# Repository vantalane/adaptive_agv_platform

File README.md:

# adaptive_agv_platform
Fontys adaptive robotics AGV platform design repository.

## Design files roadmap

Specifications and board information can be found in the "documentation" folder.

Design sources are aptly placed within design_sources folder. These include kicad files, production files and example code.

## PCBA production

Necessary files and information regarding ordering, assembly and part sourcing are packaged together with PCB versions.

These files can be found within 
``` design_sources/KiCAD/controller_mainboard_vX/production``` \
with ```vX``` being version number.

Instruction for production are found within the ```production``` folder. 
Currently, only V0.1 is available.

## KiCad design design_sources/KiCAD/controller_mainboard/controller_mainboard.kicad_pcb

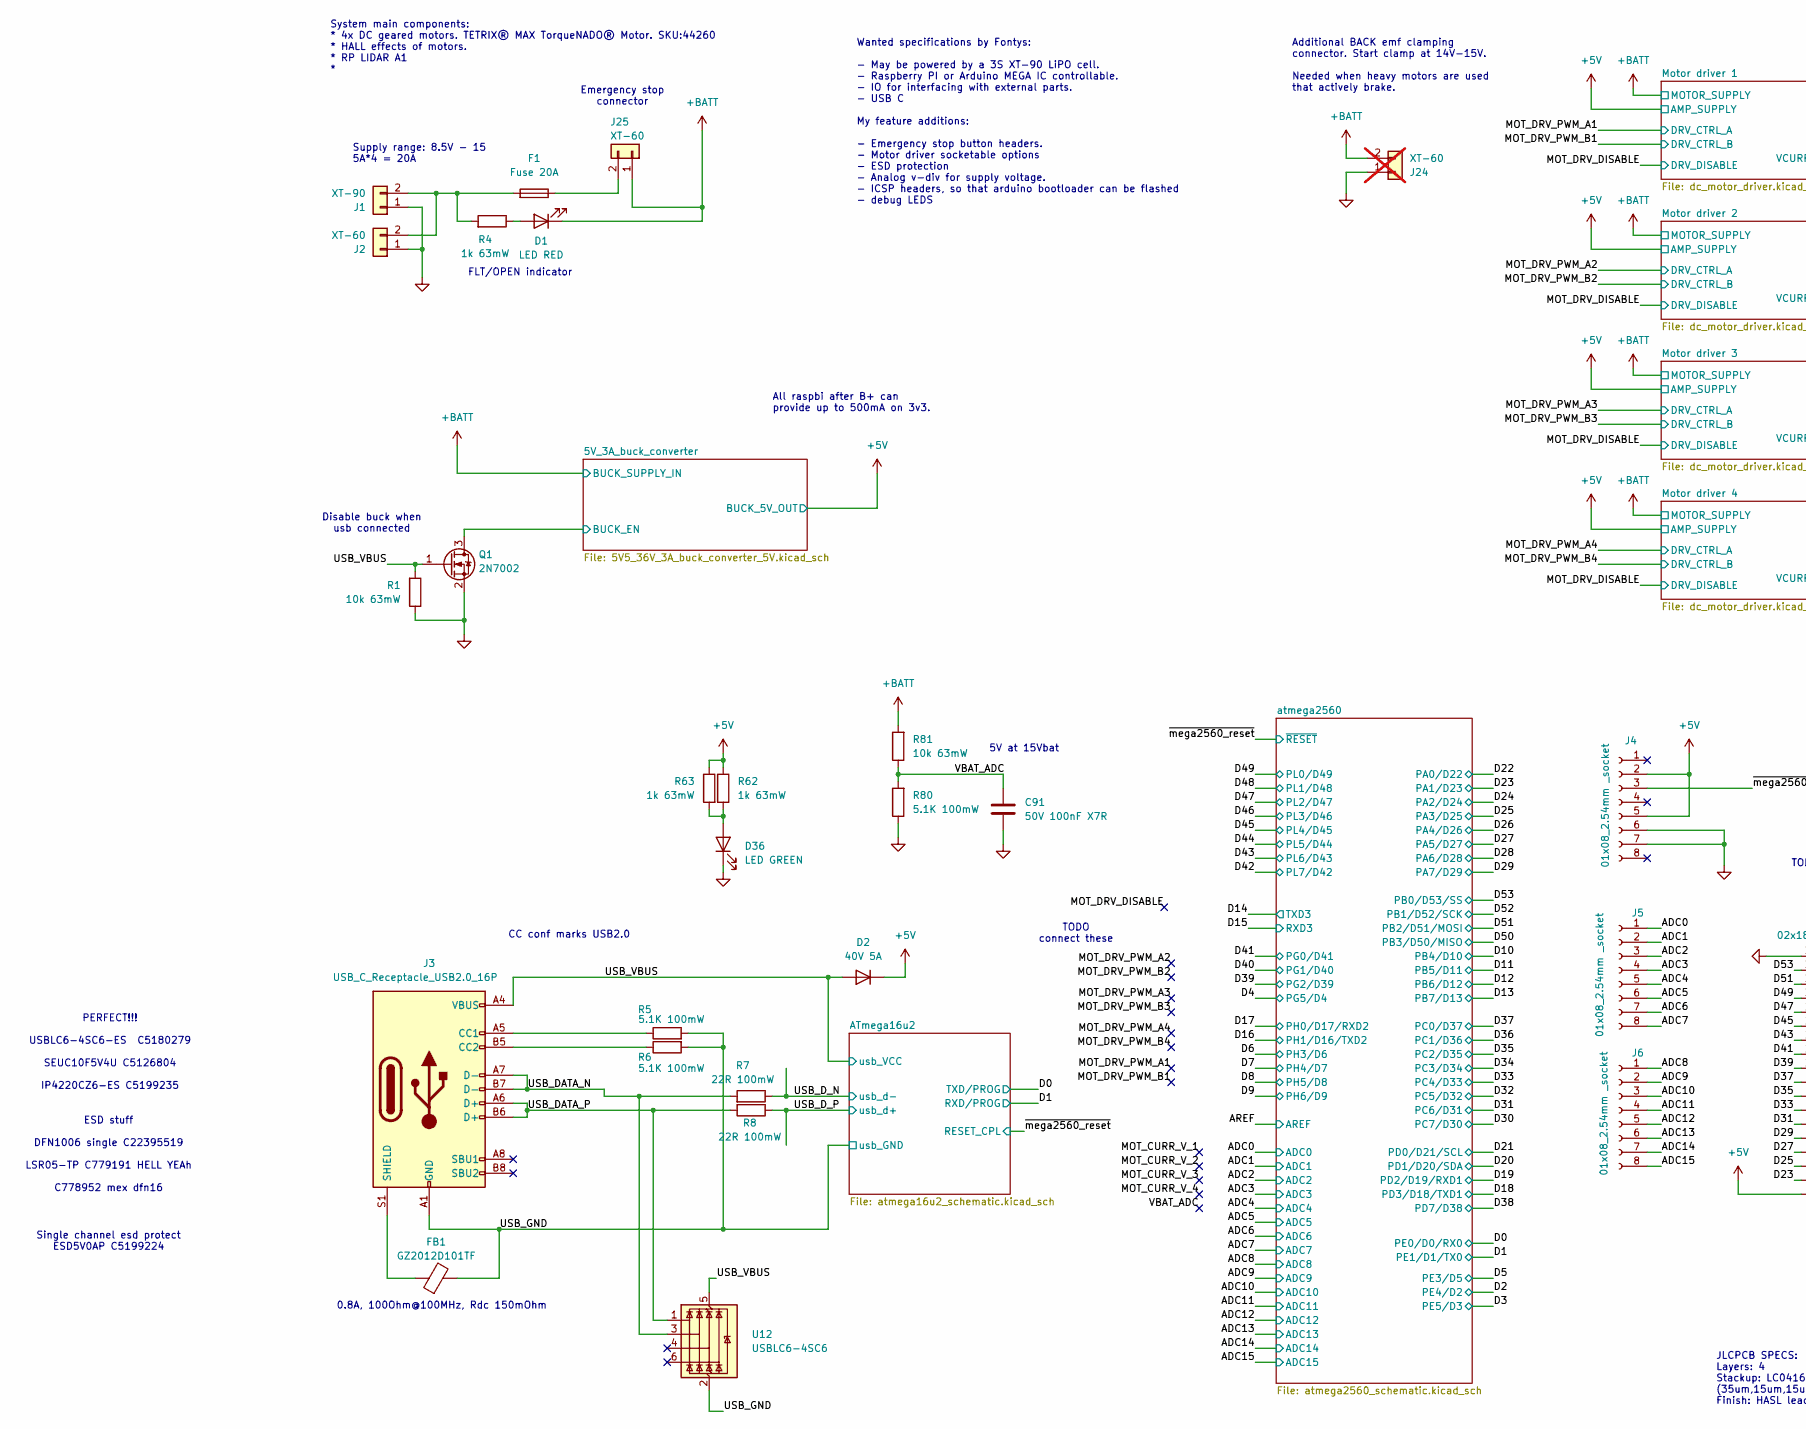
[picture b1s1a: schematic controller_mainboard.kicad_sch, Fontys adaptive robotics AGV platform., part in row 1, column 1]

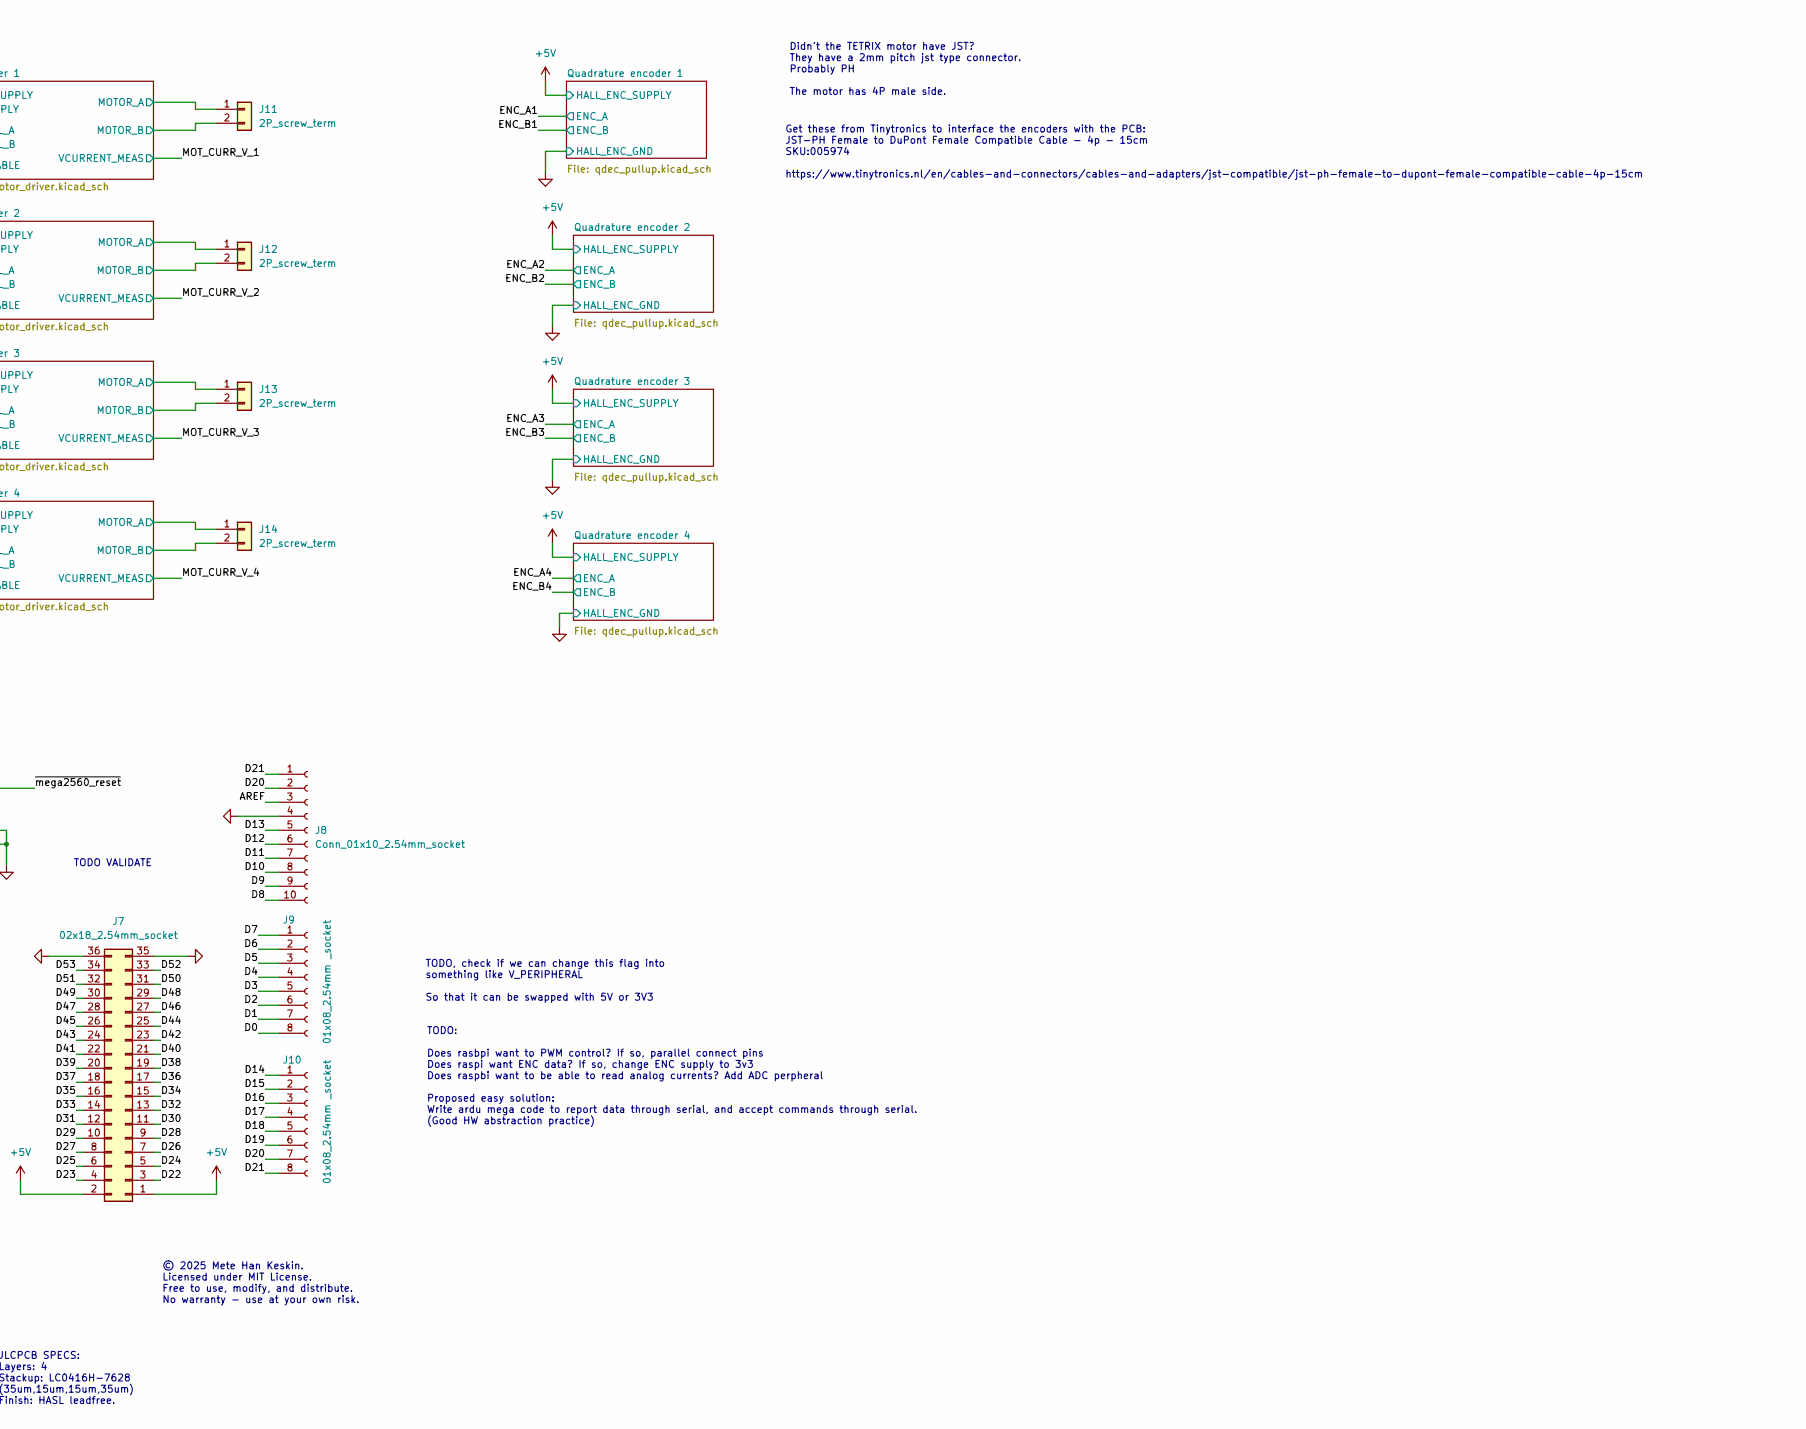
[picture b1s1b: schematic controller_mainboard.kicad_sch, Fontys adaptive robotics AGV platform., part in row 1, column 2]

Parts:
C91: 50V 100nF X7R; C_0603_1608Metric; JLCPCB C14663
D1: LED RED; LED_0603_1608Metric; JLCPCB C2286
D2: 40V 5A; D_SMA; JLCPCB C22452
D36: LED GREEN; LED_0805_2012Metric; JLCPCB C2297
F1: Fuse 20A; BLX-A fuse holder
FB1: GZ2012D101TF; L_0805_2012Metric; JLCPCB C1015
J1: XT-90; XT-90_Connector
J2, J25: XT-60; AMASS_XT60-M_1x02_P7.20mm_Vertical
J3: USB_C_Receptacle_USB2.0_16P; USB_C_Receptacle_GCT_USB4105-xx-A_16P_TopMnt_Horizontal; JLCPCB C2927038
J4, J5, J6, J9, J10: 01x08_2.54mm _socket; PinSocket_1x08_P2.54mm_Vertical
J7: 02x18_2.54mm_socket; PinHeader_2x18_P2.54mm_Vertical
J8: Conn_01x10_2.54mm_socket; PinSocket_1x10_P2.54mm_Vertical
J11, J12, J13, J14: 2P_screw_term; JST_NV_B02P-NV_1x02_P5.00mm_Vertical
J24: XT-60; AMASS_XT60-M_1x02_P7.20mm_Vertical; not fitted
Q1: 2N7002; SOT-23; JLCPCB C8545
R1, R81: 10k 63mW; R_0402_1005Metric; JLCPCB C25744
R4, R62, R63: 1k 63mW; R_0402_1005Metric; JLCPCB C11702
R5, R6, R80: 5.1K 100mW; C_0603_1608Metric; JLCPCB C23186
R7, R8: 22R 100mW; R_0603_1608Metric; JLCPCB C23345
U12: USBLC6-4SC6; SOT-23-6; JLCPCB C5180279

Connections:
+5V: D2.1 (K), J4.2, J4.5, J7.1, J7.2, R62.1, R63.1; also elsewhere on the board
+BATT: D1.1 (K), J24.2, J25.1, R81.2; also elsewhere on the board
/5V_3A_buck_converter/BUCK_EN: Q1.3 (D); also elsewhere on the board
/ADC0: J5.1; also elsewhere on the board
/ADC1: J5.2; also elsewhere on the board
/ADC2: J5.3; also elsewhere on the board
/ADC3: J5.4; also elsewhere on the board
/ADC4: J5.5; also elsewhere on the board
/ADC5: J5.6; also elsewhere on the board
/ADC6: J5.7; also elsewhere on the board
/ADC7: J5.8; also elsewhere on the board
/ADC8: J6.1; also elsewhere on the board
/ADC9: J6.2; also elsewhere on the board
/ADC10: J6.3; also elsewhere on the board
/ADC11: J6.4; also elsewhere on the board
/ADC12: J6.5; also elsewhere on the board
/ADC13: J6.6; also elsewhere on the board
/ADC14: J6.7; also elsewhere on the board
/ADC15: J6.8; also elsewhere on the board
/AREF: J8.3; also elsewhere on the board
/D0: J9.8; also elsewhere on the board
/D1: J9.7; also elsewhere on the board
/D2: J9.6; also elsewhere on the board
/D3: J9.5; also elsewhere on the board
/D4: J9.4; also elsewhere on the board
/D5: J9.3; also elsewhere on the board
/D6: J9.2; also elsewhere on the board
/D7: J9.1; also elsewhere on the board
/D8: J8.10; also elsewhere on the board
/D9: J8.9; also elsewhere on the board
/D10: J8.8; also elsewhere on the board
/D11: J8.7; also elsewhere on the board
/D12: J8.6; also elsewhere on the board
/D13: J8.5; also elsewhere on the board
/D14: J10.1; also elsewhere on the board
/D15: J10.2; also elsewhere on the board
/D16: J10.3; also elsewhere on the board
/D17: J10.4; also elsewhere on the board
/D18: J10.5; also elsewhere on the board
/D19: J10.6; also elsewhere on the board
/D20: J8.2, J10.7; also elsewhere on the board
/D21: J8.1, J10.8; also elsewhere on the board
/D22: J7.3; also elsewhere on the board
/D23: J7.4; also elsewhere on the board
/D24: J7.5; also elsewhere on the board
/D25: J7.6; also elsewhere on the board
/D26: J7.7; also elsewhere on the board
/D27: J7.8; also elsewhere on the board
/D28: J7.9; also elsewhere on the board
/D29: J7.10; also elsewhere on the board
/D30: J7.11; also elsewhere on the board
/D31: J7.12; also elsewhere on the board
/D32: J7.13; also elsewhere on the board
/D33: J7.14; also elsewhere on the board
/D34: J7.15; also elsewhere on the board
/D35: J7.16; also elsewhere on the board
/D36: J7.17; also elsewhere on the board
/D37: J7.18; also elsewhere on the board
/D38: J7.19; also elsewhere on the board
/D39: J7.20; also elsewhere on the board
/D40: J7.21; also elsewhere on the board
/D41: J7.22; also elsewhere on the board
/D42: J7.23; also elsewhere on the board
/D43: J7.24; also elsewhere on the board
/D44: J7.25; also elsewhere on the board
/D45: J7.26; also elsewhere on the board
/D46: J7.27; also elsewhere on the board
/D47: J7.28; also elsewhere on the board
/D48: J7.29; also elsewhere on the board
/D49: J7.30; also elsewhere on the board
/D50: J7.31; also elsewhere on the board
/D51: J7.32; also elsewhere on the board
/D52: J7.33; also elsewhere on the board
/D53: J7.34; also elsewhere on the board
/Motor driver 1/MOT_SIDE_A: J11.1; also elsewhere on the board
/Motor driver 1/MOT_SIDE_B: J11.2; also elsewhere on the board
/Motor driver 2/MOT_SIDE_A: J12.1; also elsewhere on the board
/Motor driver 2/MOT_SIDE_B: J12.2; also elsewhere on the board
/Motor driver 3/MOT_SIDE_A: J13.1; also elsewhere on the board
/Motor driver 3/MOT_SIDE_B: J13.2; also elsewhere on the board
/Motor driver 4/MOT_SIDE_A: J14.1; also elsewhere on the board
/Motor driver 4/MOT_SIDE_B: J14.2; also elsewhere on the board
/USB_DATA_N: J3.A7 (D-), J3.B7 (D-), R7.2, U12.3 (I/O2)
/USB_DATA_P: J3.A6 (D+), J3.B6 (D+), R8.2, U12.1 (I/O1)
/USB_D_N: R7.1; also elsewhere on the board
/USB_D_P: R8.1; also elsewhere on the board
/USB_GND: FB1.2, J3.A1 (GND), J3.A12 (GND), J3.B1 (GND), J3.B12 (GND), R5.2, R6.2, U12.2 (GND); also elsewhere on the board
/USB_VBUS: D2.2 (A), J3.A4 (VBUS), J3.A9 (VBUS), J3.B4 (VBUS), J3.B9 (VBUS), Q1.1 (G), R1.2, U12.5 (VBUS); also elsewhere on the board
/VBAT_ADC: C91.2, R80.2, R81.1
/~mega2560_reset: J4.3; also elsewhere on the board
GND: C91.1, D36.1 (K), J1.1, J2.1, J4.6, J4.7, J7.35, J7.36, J8.4, J24.1, Q1.2 (S), R1.1, R80.1; also elsewhere on the board
unnamed: D1.2 (A), R4.1
unnamed: D36.2 (A), R62.2, R63.2
unnamed: F1.2, J1.2, J2.2, R4.2
unnamed: J3.A5 (CC1), R5.1
unnamed: J3.B5 (CC2), R6.1
unnamed: FB1.1, J3.S1 (SHIELD)
unnamed: F1.1, J25.2

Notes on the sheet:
Get these from Tinytronics to interface the encoders with the PCB: JST-PH Female to DuPont Female Compatible Cable - 4p - 15cm SKU:005974 https://www.tinytronics.nl/en/cables-and-connectors/cables-and-adapters/jst-compatible/jst-ph-female-to-dupont-female-compatible-cable-4p-15cm
JLCPCB SPECS: Layers: 4 Stackup: LC0416H-7628 (35um,15um,15um,35um) Finish: HASL leadfree.
Emergency stop connector
Wanted specifications by Fontys: - May be powered by a 3S XT-90 LiPO cell. - Raspberry PI or Arduino MEGA IC controllable. - IO for interfacing with external parts. - USB C My feature additions: - Emergency stop button headers. - Motor driver socketable options - ESD protection - Analog v-div for s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
© 2025 Mete Han Keskin. Licensed under MIT License. Free to use, modify, and distribute. No warranty - use at your own risk.
5A*4 = 20A
ESD stuff DFN1006 single C22395519 LSR05-TP C779191 HELL YEAh C778952 mex dfn16
0.8A, 100Ohm@100MHz, Rdc 150mOhm
TODO VALIDATE
Supply range: 8.5V - 15
All raspbi after B+ can provide up to 500mA on 3v3.
FLT/OPEN indicator
CC conf marks USB2.0
System main components: * 4x DC geared motors. TETRIX® MAX TorqueNADO® Motor. SKU:44260 * HALL effects of motors. * RP LIDAR A1 *
Disable buck when usb connected
TODO: Does rasbpi want to PWM control? If so, parallel connect pins Does raspi want ENC data? If so, change ENC supply to 3v3 Does raspbi want to be able to read analog currents? Add ADC perpheral Proposed easy solution: Write ardu mega code to report data through serial, and accept commands throug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
Didn't the TETRIX motor have JST? They have a 2mm pitch jst type connector. Probably PH The motor has 4P male side.
TODO connect these
PERFECT!!! USBLC6-4SC6-ES C5180279 SEUC10F5V4U C5126804 IP4220CZ6-ES C5199235
5V at 15Vbat
TODO, check if we can change this flag into something like V_PERIPHERAL So that it can be swapped with 5V or 3V3
Single channel esd protect ESD5V0AP C5199224
Additional BACK emf clamping connector. Start clamp at 14V-15V. Needed when heavy motors are used that actively brake.

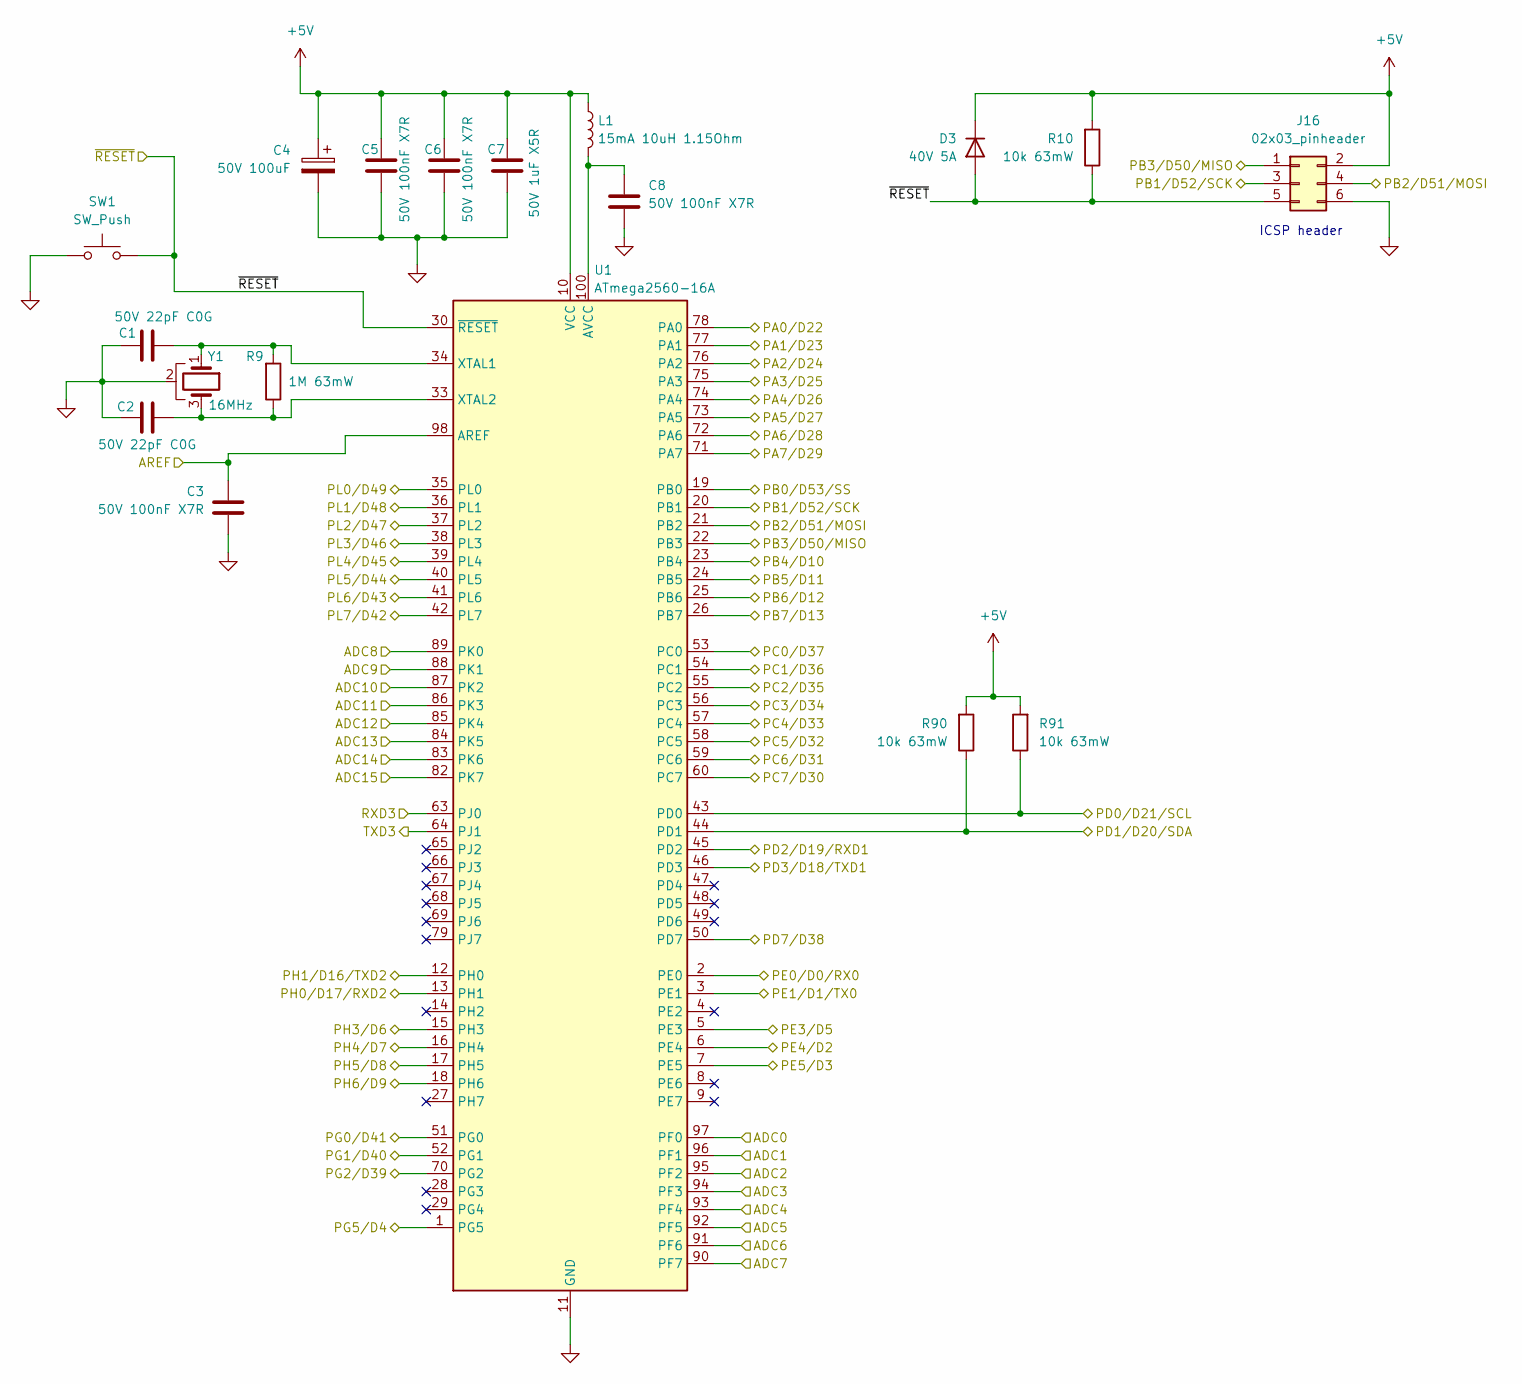
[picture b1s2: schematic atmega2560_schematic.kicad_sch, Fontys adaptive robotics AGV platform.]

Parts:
C1, C2: 50V 22pF C0G; C_0402_1005Metric; JLCPCB C1555
C3, C5, C6, C8: 50V 100nF X7R; C_0603_1608Metric; JLCPCB C14663
C4: 50V 100uF; CP_Elec_8x10.5; JLCPCB C5246561
C7: 50V 1uF X5R; C_0603_1608Metric; JLCPCB C15849
D3: 40V 5A; D_SMA; JLCPCB C22452
J16: 02x03_pinheader; PinHeader_2x03_P2.54mm_Vertical
L1: 15mA 10uH 1.15Ohm; L_0805_2012Metric; JLCPCB C1046
R9: 1M 63mW; R_0603_1608Metric
R10, R90, R91: 10k 63mW; R_0402_1005Metric; JLCPCB C25744
SW1: SW_Push; SW_SPST_PTS645; JLCPCB C19191552
U1: ATmega2560-16A; TQFP-100_14x14mm_P0.5mm
Y1: 16MHz; Resonator_SMD_Murata_CSTxExxV-3Pin_3.0x1.1mm; JLCPCB C783275

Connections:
+5V: C4.1, C5.1, C6.1, C7.1, D3.1 (K), J16.2, L1.1, R10.2, R90.2, R91.2, U1.10 (VCC), U1.31 (VCC), U1.61 (VCC), U1.80 (VCC); also elsewhere on the board
/ADC0: U1.97 (PF0); also elsewhere on the board
/ADC1: U1.96 (PF1); also elsewhere on the board
/ADC2: U1.95 (PF2); also elsewhere on the board
/ADC3: U1.94 (PF3); also elsewhere on the board
/ADC4: U1.93 (PF4); also elsewhere on the board
/ADC5: U1.92 (PF5); also elsewhere on the board
/ADC6: U1.91 (PF6); also elsewhere on the board
/ADC7: U1.90 (PF7); also elsewhere on the board
/ADC8: U1.89 (PK0); also elsewhere on the board
/ADC9: U1.88 (PK1); also elsewhere on the board
/ADC10: U1.87 (PK2); also elsewhere on the board
/ADC11: U1.86 (PK3); also elsewhere on the board
/ADC12: U1.85 (PK4); also elsewhere on the board
/ADC13: U1.84 (PK5); also elsewhere on the board
/ADC14: U1.83 (PK6); also elsewhere on the board
/ADC15: U1.82 (PK7); also elsewhere on the board
/AREF: C3.1, U1.98 (AREF); also elsewhere on the board
/D0: U1.2 (PE0); also elsewhere on the board
/D1: U1.3 (PE1); also elsewhere on the board
/D2: U1.6 (PE4); also elsewhere on the board
/D3: U1.7 (PE5); also elsewhere on the board
/D4: U1.1 (PG5); also elsewhere on the board
/D5: U1.5 (PE3); also elsewhere on the board
/D6: U1.15 (PH3); also elsewhere on the board
/D7: U1.16 (PH4); also elsewhere on the board
/D8: U1.17 (PH5); also elsewhere on the board
/D9: U1.18 (PH6); also elsewhere on the board
/D10: U1.23 (PB4); also elsewhere on the board
/D11: U1.24 (PB5); also elsewhere on the board
/D12: U1.25 (PB6); also elsewhere on the board
/D13: U1.26 (PB7); also elsewhere on the board
/D14: U1.64 (PJ1); also elsewhere on the board
/D15: U1.63 (PJ0); also elsewhere on the board
/D16: U1.12 (PH0); also elsewhere on the board
/D17: U1.13 (PH1); also elsewhere on the board
/D18: U1.46 (PD3); also elsewhere on the board
/D19: U1.45 (PD2); also elsewhere on the board
/D20: R90.1, U1.44 (PD1); also elsewhere on the board
/D21: R91.1, U1.43 (PD0); also elsewhere on the board
/D22: U1.78 (PA0); also elsewhere on the board
/D23: U1.77 (PA1); also elsewhere on the board
/D24: U1.76 (PA2); also elsewhere on the board
/D25: U1.75 (PA3); also elsewhere on the board
/D26: U1.74 (PA4); also elsewhere on the board
/D27: U1.73 (PA5); also elsewhere on the board
/D28: U1.72 (PA6); also elsewhere on the board
/D29: U1.71 (PA7); also elsewhere on the board
/D30: U1.60 (PC7); also elsewhere on the board
/D31: U1.59 (PC6); also elsewhere on the board
/D32: U1.58 (PC5); also elsewhere on the board
/D33: U1.57 (PC4); also elsewhere on the board
/D34: U1.56 (PC3); also elsewhere on the board
/D35: U1.55 (PC2); also elsewhere on the board
/D36: U1.54 (PC1); also elsewhere on the board
/D37: U1.53 (PC0); also elsewhere on the board
/D38: U1.50 (PD7); also elsewhere on the board
/D39: U1.70 (PG2); also elsewhere on the board
/D40: U1.52 (PG1); also elsewhere on the board
/D41: U1.51 (PG0); also elsewhere on the board
/D42: U1.42 (PL7); also elsewhere on the board
/D43: U1.41 (PL6); also elsewhere on the board
/D44: U1.40 (PL5); also elsewhere on the board
/D45: U1.39 (PL4); also elsewhere on the board
/D46: U1.38 (PL3); also elsewhere on the board
/D47: U1.37 (PL2); also elsewhere on the board
/D48: U1.36 (PL1); also elsewhere on the board
/D49: U1.35 (PL0); also elsewhere on the board
/D50: J16.1, U1.22 (PB3); also elsewhere on the board
/D51: J16.4, U1.21 (PB2); also elsewhere on the board
/D52: J16.3, U1.20 (PB1); also elsewhere on the board
/D53: U1.19 (PB0); also elsewhere on the board
/~mega2560_reset: D3.2 (A), J16.5, R10.1, SW1.2, U1.30 (~RESET); also elsewhere on the board
GND: C1.1, C2.1, C3.2, C4.2, C5.2, C6.2, C7.2, C8.2, J16.6, SW1.1, U1.11 (GND), U1.32 (GND), U1.62 (GND), U1.81 (GND), U1.99 (GND), Y1.2; also elsewhere on the board
unnamed: C8.1, L1.2, U1.100 (AVCC)
unnamed: C1.2, R9.2, U1.34 (XTAL1), Y1.1
unnamed: C2.2, R9.1, U1.33 (XTAL2), Y1.3

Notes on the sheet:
ICSP header

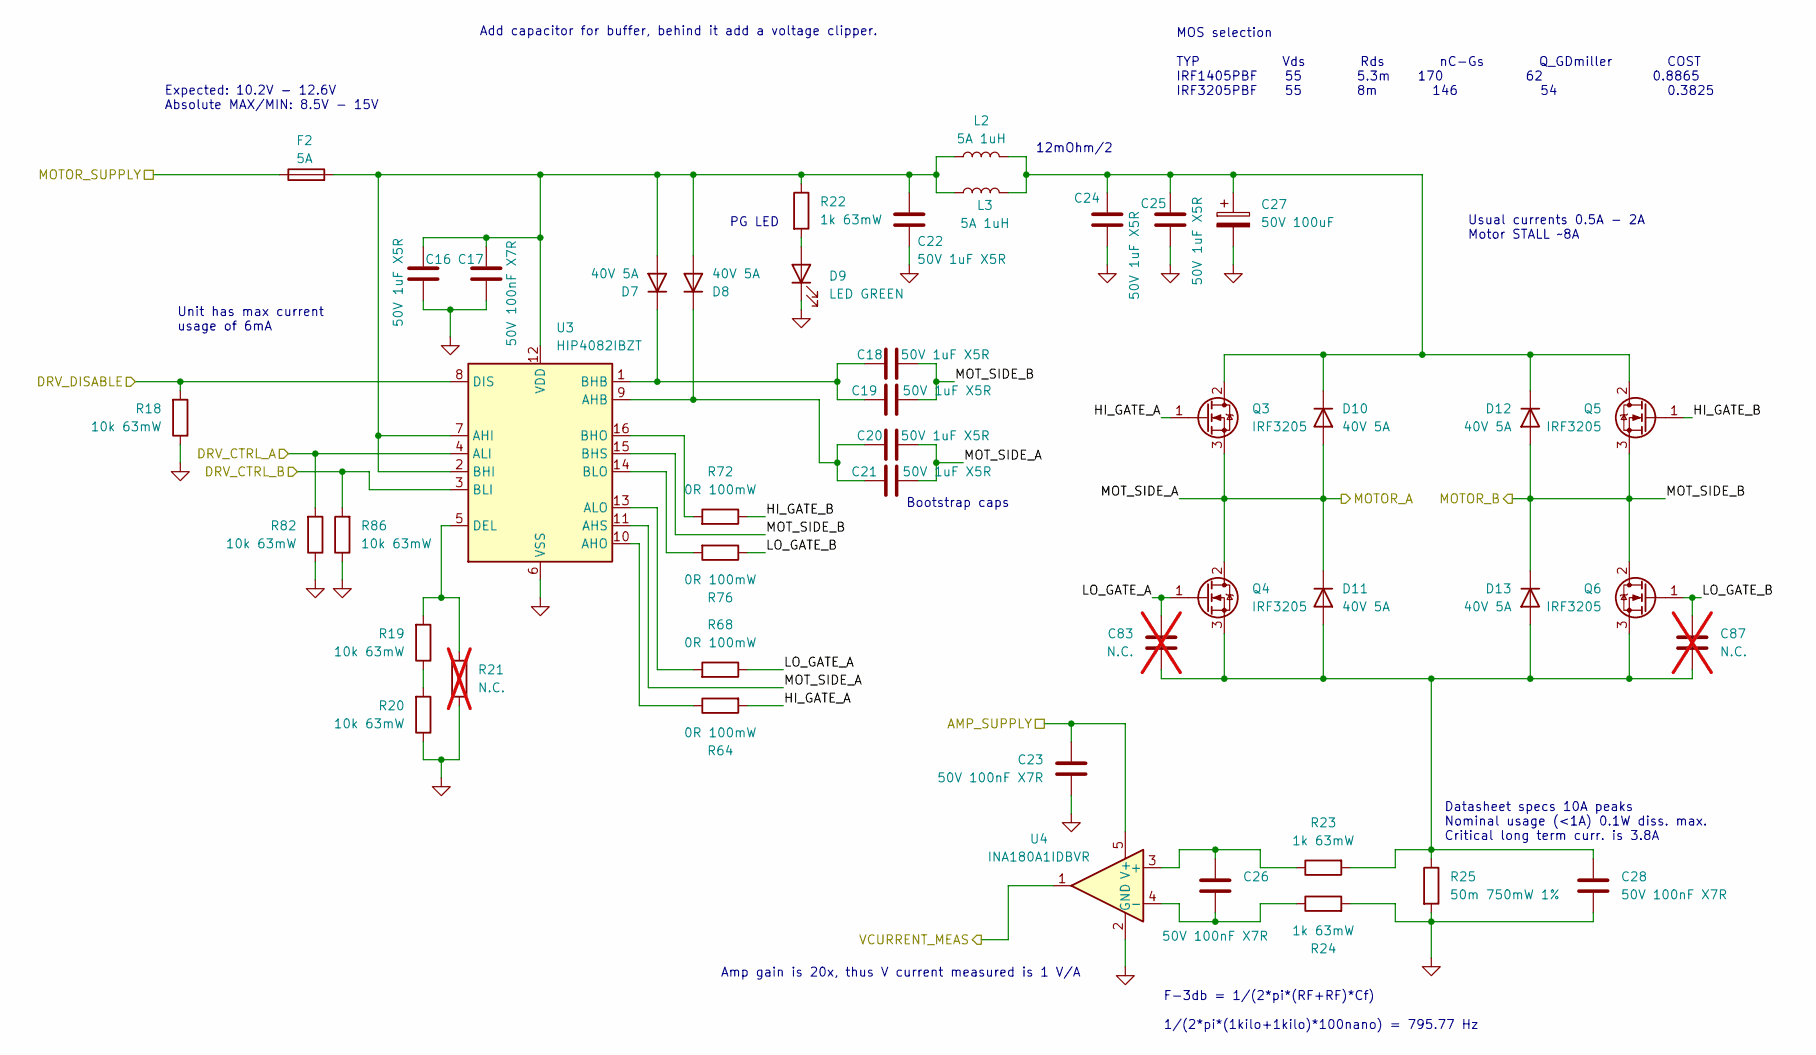
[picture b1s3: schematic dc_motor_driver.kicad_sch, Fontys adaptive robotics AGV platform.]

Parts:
C16, C18, C19, C20, C21, C22, C24, C25: 50V 1uF X5R; C_0603_1608Metric; JLCPCB C15849
C17, C23, C26, C28: 50V 100nF X7R; C_0603_1608Metric; JLCPCB C14663
C27: 50V 100uF; CP_Elec_8x10.5; JLCPCB C5246561
C83, C87: N.C.; C_0603_1608Metric; not fitted
D7, D8, D10, D11, D12, D13: 40V 5A; D_SMA; JLCPCB C22452
D9: LED GREEN; LED_0805_2012Metric; JLCPCB C2297
F2: 5A; BLX-A fuse holder
L2, L3: 5A 1uH; L_APV_ANR5040; JLCPCB C167953
Q3, Q4, Q5, Q6: IRF3205; TO-220-3_Horizontal_TabDown; JLCPCB C2561
R18, R19, R20, R82, R86: 10k 63mW; R_0402_1005Metric; JLCPCB C25744
R21: N.C.; R_0402_1005Metric; JLCPCB C25744; not fitted
R22, R23, R24: 1k 63mW; R_0402_1005Metric; JLCPCB C11702
R25: 50m 750mW 1%; R_2512_6332Metric; JLCPCB C620706
R64, R68, R72, R76: 0R 100mW; R_0603_1608Metric; JLCPCB C21189
U3: HIP4082IBZT; SOIC-16_3.9x9.9mm_P1.27mm; JLCPCB C50123
U4: INA180A1IDBVR; SOT-23-5; JLCPCB C122228

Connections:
+5V: C23.2, U4.5 (V+); also elsewhere on the board
+BATT: F2.1; also elsewhere on the board
/MOT_CURR_V_1: U4.1
/MOT_DRV_DISABLE: R18.2, U3.8 (DIS); also elsewhere on the board
/MOT_DRV_PWM_A1: R82.2, U3.4 (ALI)
/MOT_DRV_PWM_B1: R86.2, U3.3 (BLI)
/Motor driver 1/HI_GATE_A: Q3.1 (G), R64.2
/Motor driver 1/HI_GATE_B: Q5.1 (G), R72.1
/Motor driver 1/LO_GATE_A: C83.2, Q4.1 (G), R68.1
/Motor driver 1/LO_GATE_B: C87.2, Q6.1 (G), R76.1
/Motor driver 1/MOT_SIDE_A: C20.2, C21.2, D10.2 (A), D11.1 (K), Q3.3 (S), Q4.2 (D), U3.11 (AHS); also elsewhere on the board
/Motor driver 1/MOT_SIDE_B: C18.2, C19.2, D12.2 (A), D13.1 (K), Q5.3 (S), Q6.2 (D), U3.15 (BHS); also elsewhere on the board
GND: C16.2, C17.1, C22.2, C23.1, C24.2, C25.2, C27.2, C28.1, D9.1 (K), R18.1, R20.1, R21.1, R24.2, R25.2, R82.1, R86.1, U3.6 (VSS), U4.2 (GND); also elsewhere on the board
unnamed: C16.1, C17.2, C22.1, D7.2 (A), D8.2 (A), F2.2, L2.1, L3.2, R22.1, U3.2 (BHI), U3.7 (AHI), U3.12 (VDD)
unnamed: C18.1, C19.1, D7.1 (K), U3.1 (BHB)
unnamed: C20.1, C21.1, D8.1 (K), U3.9 (AHB)
unnamed: D9.2 (A), R22.2
unnamed: C24.1, C25.1, C27.1, D10.1 (K), D12.1 (K), L2.2, L3.1, Q3.2 (D), Q5.2 (D)
unnamed: C28.2, C83.1, C87.1, D11.2 (A), D13.2 (A), Q4.3 (S), Q6.3 (S), R23.2, R25.1
unnamed: R19.1, R20.2
unnamed: R64.1, U3.10 (AHO)
unnamed: R68.2, U3.13 (ALO)
unnamed: R72.2, U3.16 (BHO)
unnamed: R76.2, U3.14 (BLO)
unnamed: R19.2, R21.2, U3.5 (DEL)
unnamed: C26.2, R23.1, U4.3 (+)
unnamed: C26.1, R24.1, U4.4 (-)

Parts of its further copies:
C35, C37, C38, C39, C40, C41, C43, C44, C48, C50, C51, C52, C53, C54, C56, C57, C61, C63, C64, C65, C66, C67, C69, C70: 50V 1uF X5R; C_0603_1608Metric; JLCPCB C15849
C36, C42, C45, C47, C49, C55, C58, C60, C62, C68, C71, C73: 50V 100nF X7R; C_0603_1608Metric; JLCPCB C14663
C46, C59, C72: 50V 100uF; CP_Elec_8x10.5; JLCPCB C5246561
C84, C85, C86, C88, C89, C90: N.C.; C_0603_1608Metric; not fitted
D15, D16, D18, D19, D20, D21, D22, D23, D25, D26, D27, D28, D29, D30, D32, D33, D34, D35: 40V 5A; D_SMA; JLCPCB C22452
D17, D24, D31: LED GREEN; LED_0805_2012Metric; JLCPCB C2297
F3, F4, F5: 5A; BLX-A fuse holder
L5, L6, L7, L8, L9, L10: 5A 1uH; L_APV_ANR5040; JLCPCB C167953
Q7, Q8, Q9, Q10, Q11, Q12, Q13, Q14, Q15, Q16, Q17, Q18: IRF3205; TO-220-3_Horizontal_TabDown; JLCPCB C2561
R30, R31, R32, R38, R39, R40, R46, R47, R48, R83, R84, R85, R87, R88, R89: 10k 63mW; R_0402_1005Metric; JLCPCB C25744
R33, R41, R49: N.C.; R_0402_1005Metric; JLCPCB C25744; not fitted
R34, R35, R36, R42, R43, R44, R50, R51, R52: 1k 63mW; R_0402_1005Metric; JLCPCB C11702
R37, R45, R53: 50m 750mW 1%; R_2512_6332Metric; JLCPCB C620706
R65, R66, R67, R69, R70, R71, R73, R74, R75, R77, R78, R79: 0R 100mW; R_0603_1608Metric; JLCPCB C21189
U6, U8, U10: HIP4082IBZT; SOIC-16_3.9x9.9mm_P1.27mm; JLCPCB C50123
U7, U9, U11: INA180A1IDBVR; SOT-23-5; JLCPCB C122228

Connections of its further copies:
+5V: C42.2, C55.2, C68.2, U7.5 (V+), U9.5 (V+), U11.5 (V+); also elsewhere on the board
+BATT: F3.1, F4.1, F5.1; also elsewhere on the board
/MOT_CURR_V_2: U7.1
/MOT_CURR_V_3: U9.1
/MOT_CURR_V_4: U11.1
/MOT_DRV_DISABLE: R30.2, R38.2, R46.2, U6.8 (DIS), U8.8 (DIS), U10.8 (DIS); also elsewhere on the board
/MOT_DRV_PWM_A2: R83.2, U6.4 (ALI)
/MOT_DRV_PWM_A3: R84.2, U8.4 (ALI)
/MOT_DRV_PWM_A4: R85.2, U10.4 (ALI)
/MOT_DRV_PWM_B2: R87.2, U6.3 (BLI)
/MOT_DRV_PWM_B3: R88.2, U8.3 (BLI)
/MOT_DRV_PWM_B4: R89.2, U10.3 (BLI)
/Motor driver 2/HI_GATE_A: Q7.1 (G), R65.2
/Motor driver 2/HI_GATE_B: Q9.1 (G), R73.1
/Motor driver 2/LO_GATE_A: C84.2, Q8.1 (G), R69.1
/Motor driver 2/LO_GATE_B: C88.2, Q10.1 (G), R77.1
/Motor driver 2/MOT_SIDE_A: C39.2, C40.2, D18.2 (A), D19.1 (K), Q7.3 (S), Q8.2 (D), U6.11 (AHS); also elsewhere on the board
/Motor driver 2/MOT_SIDE_B: C37.2, C38.2, D20.2 (A), D21.1 (K), Q9.3 (S), Q10.2 (D), U6.15 (BHS); also elsewhere on the board
/Motor driver 3/HI_GATE_A: Q11.1 (G), R66.2
/Motor driver 3/HI_GATE_B: Q13.1 (G), R74.1
/Motor driver 3/LO_GATE_A: C85.2, Q12.1 (G), R70.1
/Motor driver 3/LO_GATE_B: C89.2, Q14.1 (G), R78.1
/Motor driver 3/MOT_SIDE_A: C52.2, C53.2, D25.2 (A), D26.1 (K), Q11.3 (S), Q12.2 (D), U8.11 (AHS); also elsewhere on the board
/Motor driver 3/MOT_SIDE_B: C50.2, C51.2, D27.2 (A), D28.1 (K), Q13.3 (S), Q14.2 (D), U8.15 (BHS); also elsewhere on the board
/Motor driver 4/HI_GATE_A: Q15.1 (G), R67.2
/Motor driver 4/HI_GATE_B: Q17.1 (G), R75.1
/Motor driver 4/LO_GATE_A: C86.2, Q16.1 (G), R71.1
/Motor driver 4/LO_GATE_B: C90.2, Q18.1 (G), R79.1
/Motor driver 4/MOT_SIDE_A: C65.2, C66.2, D32.2 (A), D33.1 (K), Q15.3 (S), Q16.2 (D), U10.11 (AHS); also elsewhere on the board
/Motor driver 4/MOT_SIDE_B: C63.2, C64.2, D34.2 (A), D35.1 (K), Q17.3 (S), Q18.2 (D), U10.15 (BHS); also elsewhere on the board
GND: C35.2, C36.1, C41.2, C42.1, C43.2, C44.2, C46.2, C47.1, C48.2, C49.1, C54.2, C55.1, C56.2, C57.2, C59.2, C60.1, C61.2, C62.1, C67.2, C68.1, C69.2, C70.2, C72.2, C73.1, D17.1 (K), D24.1 (K), D31.1 (K), R30.1, R32.1, R33.1, R36.2, R37.2, R38.1, R40.1, R41.1, R44.2, R45.2, R46.1, R48.1, R49.1, R52.2, R53.2, R83.1, R84.1, R85.1, R87.1, R88.1, R89.1, U6.6 (VSS), U7.2 (GND), U8.6 (VSS), U9.2 (GND), U10.6 (VSS), U11.2 (GND); also elsewhere on the board
unnamed: C35.1, C36.2, C41.1, D15.2 (A), D16.2 (A), F3.2, L5.1, L6.2, R34.1, U6.2 (BHI), U6.7 (AHI), U6.12 (VDD)
unnamed: C37.1, C38.1, D15.1 (K), U6.1 (BHB)
unnamed: C39.1, C40.1, D16.1 (K), U6.9 (AHB)
unnamed: D17.2 (A), R34.2
unnamed: C43.1, C44.1, C46.1, D18.1 (K), D20.1 (K), L5.2, L6.1, Q7.2 (D), Q9.2 (D)
unnamed: C47.2, C84.1, C88.1, D19.2 (A), D21.2 (A), Q8.3 (S), Q10.3 (S), R35.2, R37.1
unnamed: C48.1, C49.2, C54.1, D22.2 (A), D23.2 (A), F4.2, L7.1, L8.2, R42.1, U8.2 (BHI), U8.7 (AHI), U8.12 (VDD)
unnamed: C50.1, C51.1, D22.1 (K), U8.1 (BHB)
unnamed: C52.1, C53.1, D23.1 (K), U8.9 (AHB)
unnamed: D24.2 (A), R42.2
unnamed: C56.1, C57.1, C59.1, D25.1 (K), D27.1 (K), L7.2, L8.1, Q11.2 (D), Q13.2 (D)
unnamed: C60.2, C85.1, C89.1, D26.2 (A), D28.2 (A), Q12.3 (S), Q14.3 (S), R43.2, R45.1
unnamed: C61.1, C62.2, C67.1, D29.2 (A), D30.2 (A), F5.2, L9.1, L10.2, R50.1, U10.2 (BHI), U10.7 (AHI), U10.12 (VDD)
unnamed: C63.1, C64.1, D29.1 (K), U10.1 (BHB)
unnamed: C65.1, C66.1, D30.1 (K), U10.9 (AHB)
unnamed: D31.2 (A), R50.2
unnamed: C69.1, C70.1, C72.1, D32.1 (K), D34.1 (K), L9.2, L10.1, Q15.2 (D), Q17.2 (D)
unnamed: C73.2, C86.1, C90.1, D33.2 (A), D35.2 (A), Q16.3 (S), Q18.3 (S), R51.2, R53.1
unnamed: R31.1, R32.2
unnamed: R39.1, R40.2
unnamed: R47.1, R48.2
unnamed: R65.1, U6.10 (AHO)
unnamed: R69.2, U6.13 (ALO)
unnamed: R73.2, U6.16 (BHO)
unnamed: R77.2, U6.14 (BLO)
unnamed: R31.2, R33.2, U6.5 (DEL)
unnamed: C45.2, R35.1, U7.3 (+)
unnamed: C45.1, R36.1, U7.4 (-)
unnamed: R66.1, U8.10 (AHO)
unnamed: R70.2, U8.13 (ALO)
unnamed: R74.2, U8.16 (BHO)
unnamed: R78.2, U8.14 (BLO)
unnamed: R39.2, R41.2, U8.5 (DEL)
unnamed: C58.2, R43.1, U9.3 (+)
unnamed: C58.1, R44.1, U9.4 (-)
unnamed: R67.1, U10.10 (AHO)
unnamed: R71.2, U10.13 (ALO)
unnamed: R75.2, U10.16 (BHO)
unnamed: R79.2, U10.14 (BLO)
unnamed: R47.2, R49.2, U10.5 (DEL)
unnamed: C71.2, R51.1, U11.3 (+)
unnamed: C71.1, R52.1, U11.4 (-)

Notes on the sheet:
Usual currents 0.5A - 2A Motor STALL ~8A
PG LED
Expected: 10.2V - 12.6V Absolute MAX/MIN: 8.5V - 15V
F-3db = 1/(2*pi*(RF+RF)*Cf) 1/(2*pi*(1kilo+1kilo)*100nano) = 795.77 Hz
Bootstrap caps
Amp gain is 20x, thus V current measured is 1 V/A
Add capacitor for buffer, behind it add a voltage clipper.
12mOhm/2
Datasheet specs 10A peaks Nominal usage (<1A) 0.1W diss. max. Critical long term curr. is 3.8A
MOS selection TYP Vds Rds nC-Gs Q_GDmiller COST IRF1405PBF 55 5.3m 170 62 0.8865 IRF3205PBF 55 8m 146 54 0.3825
Unit has max current usage of 6mA

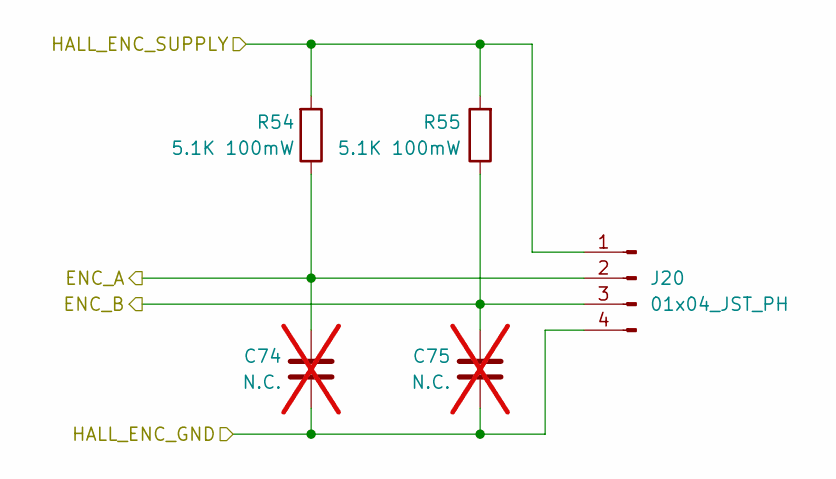
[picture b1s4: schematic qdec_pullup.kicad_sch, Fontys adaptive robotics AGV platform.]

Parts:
C74, C75: N.C.; C_0603_1608Metric; not fitted
J20: 01x04_JST_PH; JST_PH_B4B-PH-K_1x04_P2.00mm_Vertical
R54, R55: 5.1K 100mW; C_0603_1608Metric; JLCPCB C23186

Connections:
+5V: J20.1, R54.2, R55.2; also elsewhere on the board
/ENC_A1: C74.2, J20.2, R54.1
/ENC_B1: C75.2, J20.3, R55.1
GND: C74.1, C75.1, J20.4; also elsewhere on the board

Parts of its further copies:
C76, C77, C78, C79, C80, C81: N.C.; C_0603_1608Metric; not fitted
J21, J22, J23: 01x04_JST_PH; JST_PH_B4B-PH-K_1x04_P2.00mm_Vertical
R56, R57, R58, R59, R60, R61: 5.1K 100mW; C_0603_1608Metric; JLCPCB C23186

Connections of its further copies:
+5V: J21.1, J22.1, J23.1, R56.2, R57.2, R58.2, R59.2, R60.2, R61.2; also elsewhere on the board
/ENC_A2: C76.2, J21.2, R56.1
/ENC_A3: C78.2, J22.2, R58.1
/ENC_A4: C80.2, J23.2, R60.1
/ENC_B2: C77.2, J21.3, R57.1
/ENC_B3: C79.2, J22.3, R59.1
/ENC_B4: C81.2, J23.3, R61.1
GND: C76.1, C77.1, C78.1, C79.1, C80.1, C81.1, J21.4, J22.4, J23.4; also elsewhere on the board

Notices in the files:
design_sources/KiCAD/controller_mainboard/5V5_36V_3A_buck_converter_5V.kicad_sch:
MIT License. Copyright (c) 2025 kestech.net
design_sources/KiCAD/controller_mainboard/controller_mainboard.kicad_pcb:
Copyright © Mete Han Keskin, 2025
MIT License
